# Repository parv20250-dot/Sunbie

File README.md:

# Sunbie

Sunbie is a Tamagotchi inspired product that utilises a Waveshare ESP 32- C3 microprocessor.
It uses sensors such as the ADXL345 and the DHT11 so as to gather data from the environment, it also has a sprite (in this case a fox) 
that responds to any changes in the temperature. The accelerometer enables the user to interact with the sprite so as to feed her, play with her,
pet her or (if she's sick) give her meds. You look after it by tilting the device to pick actions from a menu.

## PCB Diagram and 3d view

## Schematic

The above image contains the schematic that the PCB diagram is made with reference to,  labels have been used for different nets so as to make the schematic look cleaner.

## Actions

| Action | Joy | Energy | Fullness | Health |
|---|---|---|---|---|
| Nap | +1 | +18 | −4 | +3 |
| Play | +12 | −9 | −5 | −4 |
| Feed | +3 | −2 | +15 | +1 |
| Pet | +7 | +2 | 0 | 0 |
| Meds | −7 | −3 | 0 | +7 |

A 3d visual of the device on Kicad

## Why was this made?

This was made as a part of Hack Club's Half Life programme.

## Who is the sprite?

The sprite (pet) can be set to anything the user desires by changing the Bit Image in the source code. However, I use a fox.
inspired by the image below.

The code is written in C++ Arduino framework and uses an SSDI306 OLED to display the fox and menu, an ADXL345 in order to detect tilts and also detect shaking (shake/dizzy pet reactions), a DHT11 for temperature and humidity readings and temperature reactions, and a buzzer for sounds. The pet is saved, it can be reset by setting RESET_SAVED_PET to true,uploading it and then setting it to false again!!

## BOM
|Item|Part_Name                                                      |Description                                                                    |Quantity|Unit_Cost|Total_Cost|Supplier   |
|----|---------------------------------------------------------------|-------------------------------------------------------------------------------|--------|---------|----------|-----------|
|1   |DHT-11 temperature and humidity sensor                         |It senses differences in the surroundings which react.                         |1       |3.91     |3.91      |electro:kit|
|2   |Resistor                                                       |Resistor for DHT11 data line                                                   |1       |0.10     |0.10      |electro:kit|
|3   |ADXL345 - I2C SPI                                              |Accelerometer(motion sensor) it detects motion allowing for the Sunbie to react|1       |6.90     |6.90      |electro:kit|
|4   |ESP32-C3 developmentboard mini 4MB                             |The main controls,microprocessor in sunbie                                     |1       |7.90     |7.90      |electro:kit|
|5   |OLED Display 0.96 inch I2C 128x64 pixels for RPi/Arduino/Atmega|Display for sunbie, allows it to show responses                                |1       |6.50     |6.50      |jmux.se    |
|6   |pcb                                                            |Main part/base of whole pcb                                                    |1       |4.00     |4.00      |jlc pcb    |
|7   |Passive piezo buzzer 70dB PS12 PCB ø12x6.5mm                   |play sound alongside reactions                                                 |1       |0.75     |0.75      |electro:kit|
|8   |WS Standard Linear Switch                                      |Interaction with the device                                                    |2       |0.15     |0.30      |Max Gaming |
|9   |Tax & shipping                                                 |for the whole order                                                            |-       |-        |2.00      |-          |

## Credits
Made for Hack Club-Half Life

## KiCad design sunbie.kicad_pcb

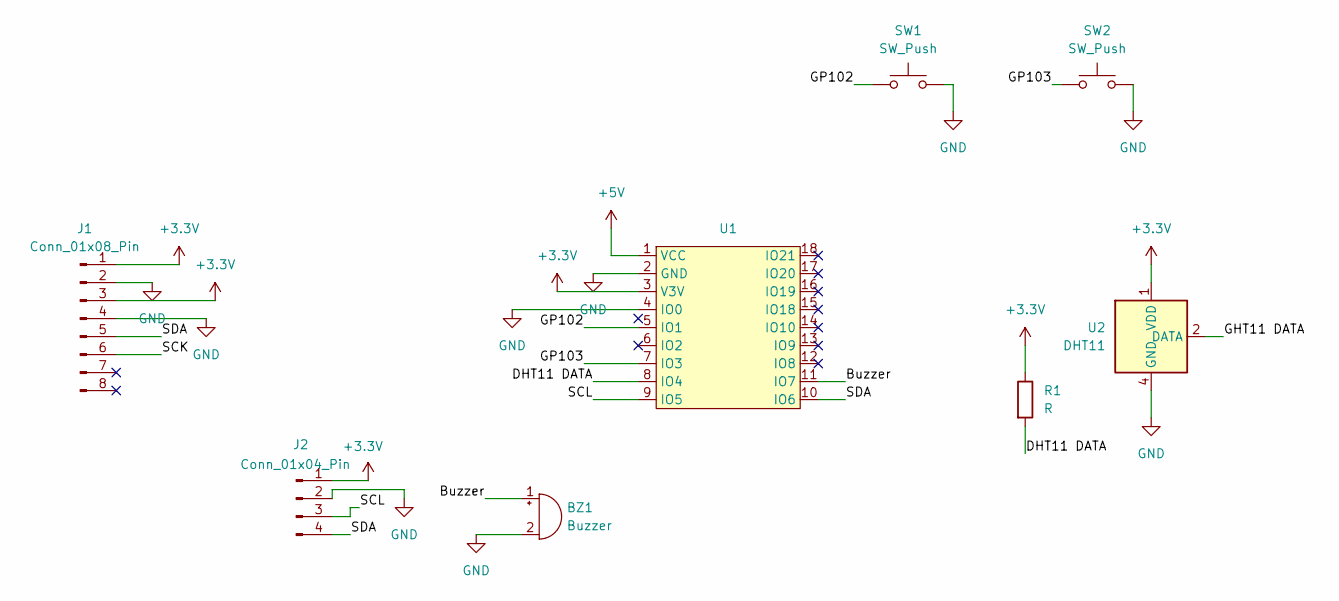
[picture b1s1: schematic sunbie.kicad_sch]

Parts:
BZ1: Buzzer; Buzzer_12x9.5RM7.6
J1: Conn_01x08_Pin; PinHeader_1x08_P2.54mm_Vertical
J2: Conn_01x04_Pin; Display_128x64_096_I2C
R1: R; R_Axial_DIN0204_L3.6mm_D1.6mm_P7.62mm_Horizontal
SW1, SW2: SW_Push; SW_Cherry_MX_1.00u_PCB
U1: Waveshare-ESP32-C3-Zero
U2: DHT11; Aosong_DHT11_5.5x12.0_P2.54mm

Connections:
+3.3V: J1.1, J1.3, J2.1, R1.1, U1.3 (V3V), U2.1 (VDD)
+5V: U1.1 (VCC)
/Buzzer: BZ1.1 (+), U1.11 (IO7)
/DHT11 DATA: R1.2, U1.8 (IO4)
/GHT11 DATA: U2.2 (DATA)
/GP102: SW1.1, U1.5 (IO1)
/GP103: SW2.1, U1.7 (IO3)
/SCK: J1.6
/SCL: J2.3, U1.9 (IO5)
/SDA: J1.5, J2.4, U1.10 (IO6)
GND: BZ1.2 (-), J1.2, J1.4, J2.2, SW1.2, SW2.2, U1.2 (GND), U1.4 (IO0), U2.4 (GND)

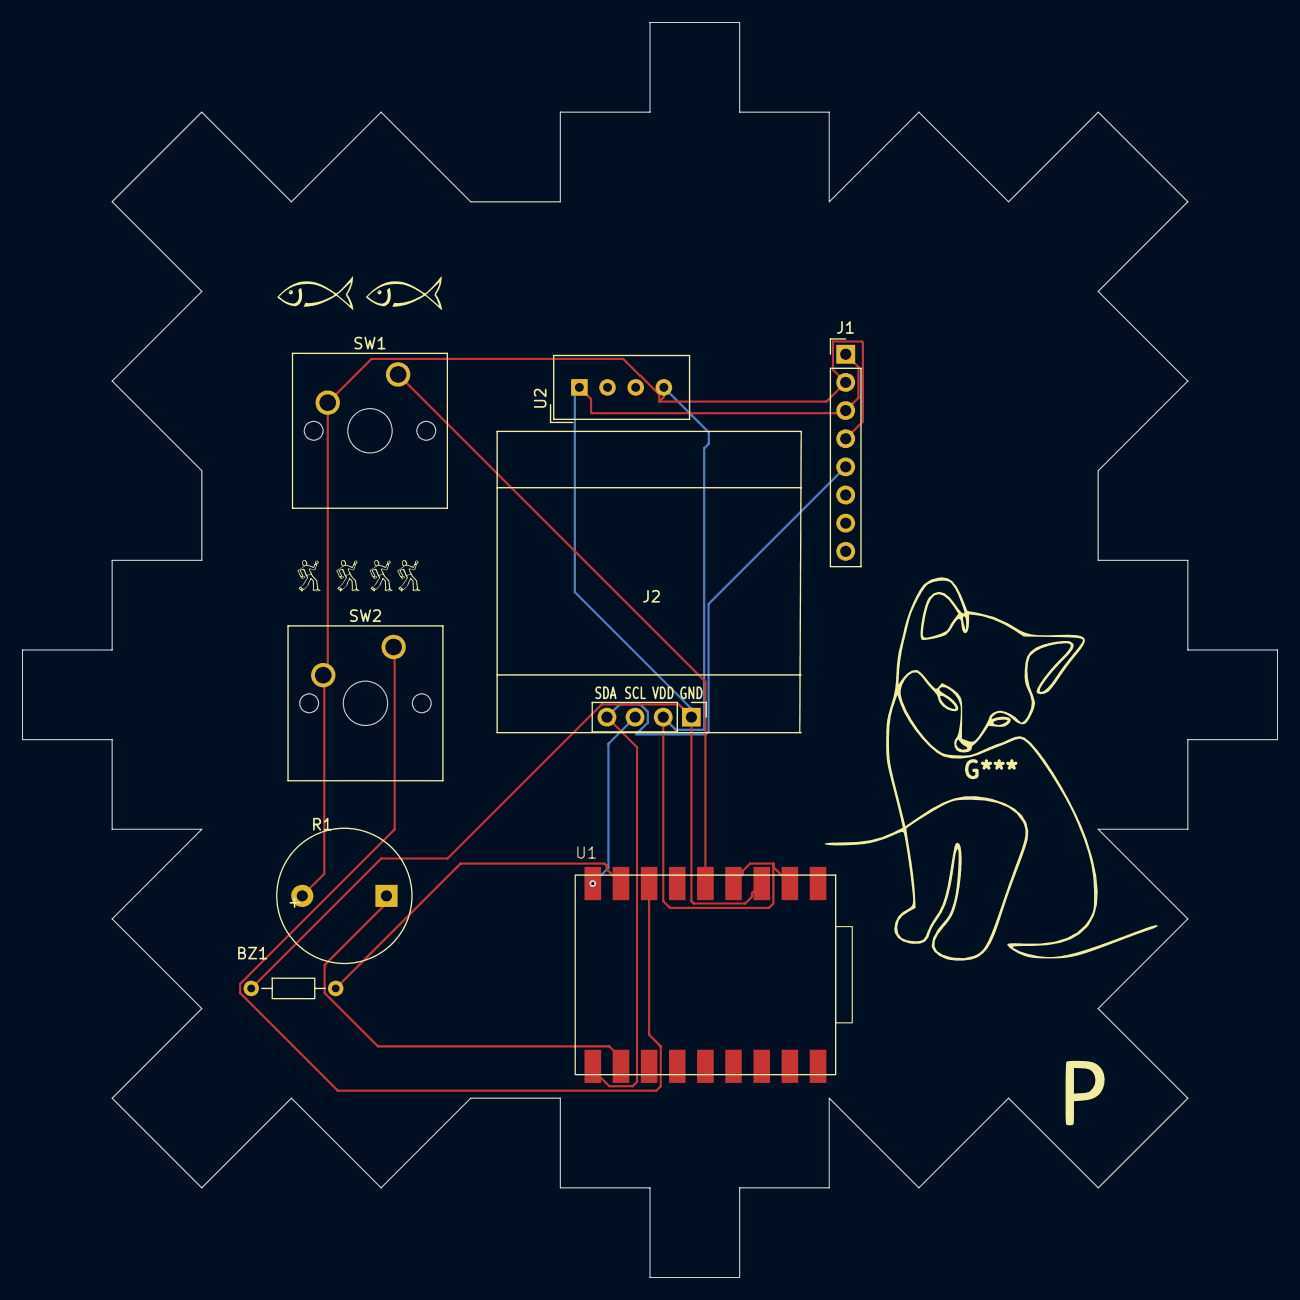
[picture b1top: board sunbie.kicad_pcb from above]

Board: 2 copper layers, 113.2 x 113.2 mm, 8 parts (0 on the bottom side), 8 nets.
